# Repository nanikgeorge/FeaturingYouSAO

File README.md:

# Featuring You!
This is an SAO I designed to share at Hackaday Supercon 2024.

Supercon badges are awesome! But for some reason they don't always have a spot to put your name, this is my solution. An SAO that looks like one of those big red flashing arrows - featuring you!

What is an SAO? Here's a Hackaday article about that: [https://hackaday.com/2019/03/20/introducing-the-shitty-add-on-v1-69bis-standard/](https://hackaday.com/2019/03/20/introducing-the-shitty-add-on-v1-69bis-standard/)

Interested in attending Hackaday Supercon 2024? Last year was a lot of fun - this year I'm speaking so make sure to check it out: [https://hackaday.io/superconference/](https://hackaday.io/superconference/)

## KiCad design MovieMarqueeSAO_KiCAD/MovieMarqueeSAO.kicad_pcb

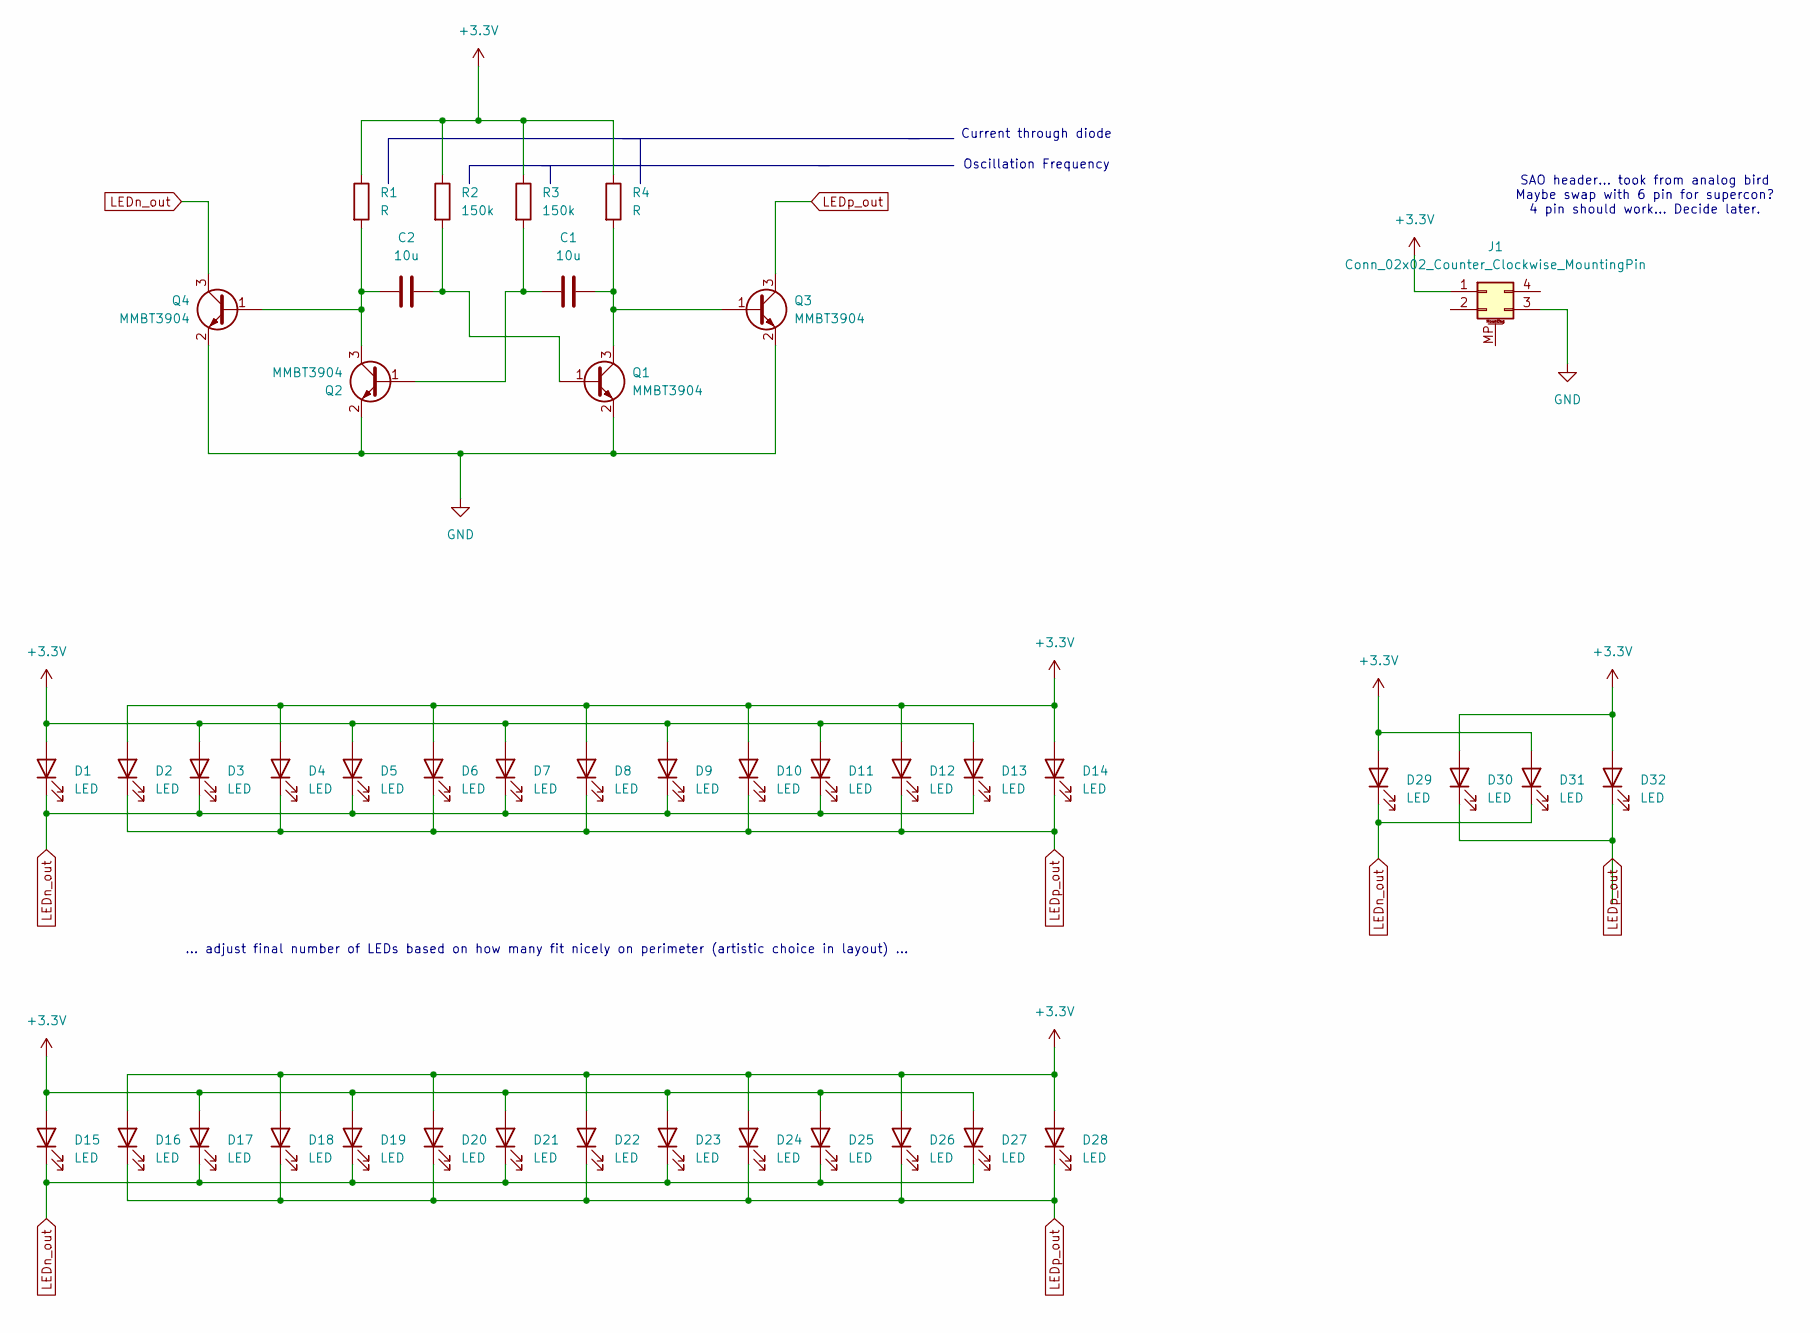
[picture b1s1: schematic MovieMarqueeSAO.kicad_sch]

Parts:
C1, C2: 10u; C_0603_1608Metric
D1, D2, D3, D4, D5, D6, D7, D8, D9, D10, D11, D12, D13, D14, D15, D16, D17, D18, D19, D20, D21, D22, D23, D24, D25, D26, D27, D28, D29, D30, D31, D32: LED; D_0603_1608Metric
J1: Conn_02x02_Counter_Clockwise_MountingPin; PinHeader_2x02_P2.54mm_Vertical
Q1, Q2, Q3, Q4: MMBT3904; SOT-23
R1, R4: R; R_0603_1608Metric
R2, R3: 150k; R_0603_1608Metric

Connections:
+3.3V: D1.2 (A), D2.2 (A), D3.2 (A), D4.2 (A), D5.2 (A), D6.2 (A), D7.2 (A), D8.2 (A), D9.2 (A), D10.2 (A), D11.2 (A), D12.2 (A), D13.2 (A), D14.2 (A), D15.2 (A), D16.2 (A), D17.2 (A), D18.2 (A), D19.2 (A), D20.2 (A), D21.2 (A), D22.2 (A), D23.2 (A), D24.2 (A), D25.2 (A), D26.2 (A), D27.2 (A), D28.2 (A), D29.2 (A), D30.2 (A), D31.2 (A), D32.2 (A), J1.1, R1.1, R2.1, R3.1, R4.1
GND: J1.3, Q1.2 (E), Q2.2 (E), Q3.2 (E), Q4.2 (E)
LEDn_out: D1.1 (K), D3.1 (K), D5.1 (K), D7.1 (K), D9.1 (K), D11.1 (K), D13.1 (K), D15.1 (K), D17.1 (K), D19.1 (K), D21.1 (K), D23.1 (K), D25.1 (K), D27.1 (K), D29.1 (K), D31.1 (K), Q4.3 (C)
LEDp_out: D2.1 (K), D4.1 (K), D6.1 (K), D8.1 (K), D10.1 (K), D12.1 (K), D14.1 (K), D16.1 (K), D18.1 (K), D20.1 (K), D22.1 (K), D24.1 (K), D26.1 (K), D28.1 (K), D30.1 (K), D32.1 (K), Q3.3 (C)
unnamed: C2.2, Q1.1 (B), R2.2
unnamed: C1.2, Q1.3 (C), Q3.1 (B), R4.2
unnamed: C1.1, Q2.1 (B), R3.2
unnamed: C2.1, Q2.3 (C), Q4.1 (B), R1.2

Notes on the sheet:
SAO header... took from analog bird Maybe swap with 6 pin for supercon? 4 pin should work... Decide later.
Oscillation Frequency
Current through diode
... adjust final number of LEDs based on how many fit nicely on perimeter (artistic choice in layout) ...

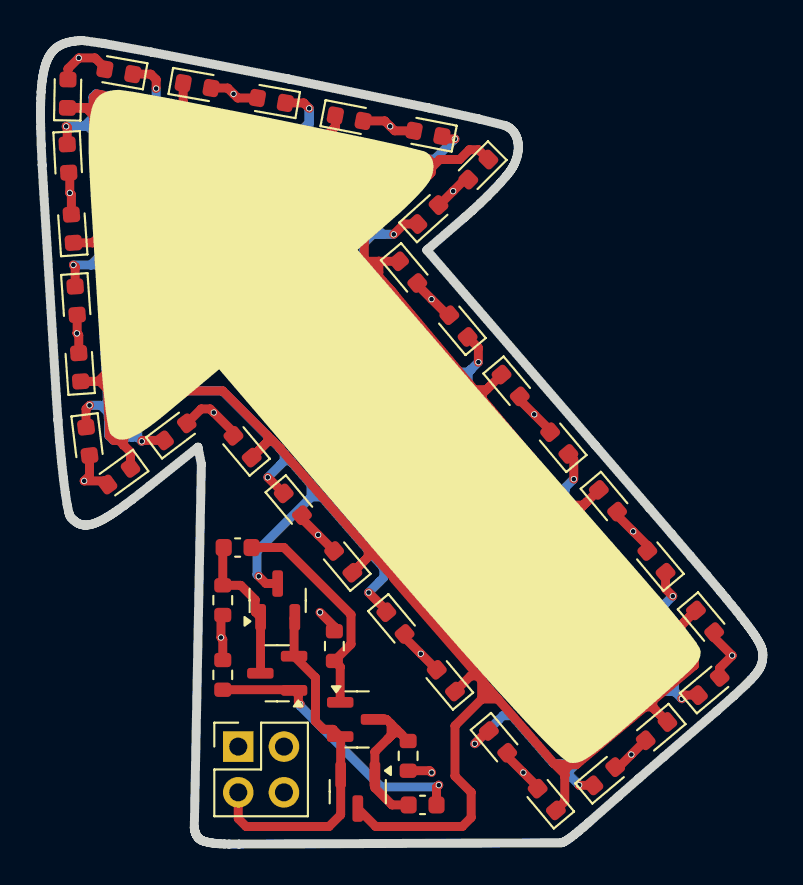
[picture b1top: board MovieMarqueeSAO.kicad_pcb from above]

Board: 2 copper layers, 40.1 x 44.6 mm, 43 parts (0 on the bottom side), 8 nets.

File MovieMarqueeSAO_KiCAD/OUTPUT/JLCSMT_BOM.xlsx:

Comment | Designator | Footprint | JLCPCB Part #（optional）
header | J1 | PinHeader_2x02_P2.54mm_Vertical
White LED | D32,D31,D30,D29,D28,D27,D26,D25,D24,D23,D22,D21,D20,D19,D18,D17,D16,D15,D14,D13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 | D_0603_1608Metric | C2290
5.6K Resistor | R4,R1 | R_0603_1608Metric | C23189
150K Resistor | R3,R2 | R_0603_1608Metric | C22807
MMBT3904 | Q4,Q2,Q1,Q3 | SOT-23 | C20526
10u Capacitor | C2,C1 | C_0603_1608Metric

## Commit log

2024-10-21 initial commit - everything is already done because I forgot to setup version control when I was working on it
2024-10-21 removed unnecessary files
2024-10-21 added readme
